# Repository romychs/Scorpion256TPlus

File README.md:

# Scorpion ZS-256 Turbo+

## Российский клон компьютера ZX Spectrum с улучшениями.

Компьютер разрабатывался и выпускался, под руководством Сергея Зонова, санкт-петербургской фирмой Scorpion с 1996 по 1998г.
Данная версия схемы, отревершена по файлам molodcov_alex, а затем и по плате Павла Рябцова известной как "Black Edition".
Изначально это была схема, которая упоминается как схема Черного кота. В создании схемы, большую помощь оказали труды savelij из темы про скорпиона 1024.

## Особенности:
- Z80B CPU, режим Turbo 7MHz, данный вариант хорошо работает с КМОП процессорами Z84C0020PEC.
- 256k DRAM, хорошо работают только импортные микросхемы типа 41256.
- Теневой Сервис-Монитор
- Музыкальный сопроцессор AY-3-8912.
- 2 Слота расширения ZX Bus.
- Контроллер дисковода Floppy-дисков с ФАПЧ.
- Старые микросхемы 565РТ5 заменены более доступными GAL16V8, GAL22V10.
- PROF ROM.
- Интерфейс Centronics для принтера.
- Интерфейс RS-232, но никто не проверял, работает ли?

[Принципиальная схема](Export/Schematic_Scorpion-256-Turbo_v16.2.8.pdf)

[Монтажная схема](Export/PCB_SILK_TOP_v16.2.8.pdf)

Печатная плата и герберы, получены, как побочный продукт при реверсе схемы и отличаются и от платы molodcov_alex и от платы Павла. Многие уже собирали платы версий до v16.2.3. 
Некоторые трассы укорочены, уменьшено число изгибов проводников, уменьшено число проводников между ножками процессора с 3-х до 2-х.
На плате нет краевых разъемов.

[Тема на форуме, по данному варианту компьютера](https://zx-pk.ru/threads/9195-scorpion-zs-256-turbo-restored)

[Чат ZS Scorpion  в Telegram](https://t.me/zs_scorpion)

## Внимание!
- На платах v16.2.4 и v16.2.5 на шелкографии обнаружена ошибка. Все транзисторы КТ315 и КТ361, нужно запаивать эмиттером в отверстие с квадратным падом.

## Изменения
- В версии v16.2, исправлено подключение GAL ФАПЧ контроллера дисковода. Несоответствие было обнаружено при сборке платы пользователем форума tigr101274. Исправлена печатная плата в соответствии со схемой, на печатной плате значительно расширены проводники питания за счет полигонов.
- В версии v16.2.1 исправлена ошибка, замеченная azx987sa, с сигналом строба интерфейса принтера.
- В версии v16.2.2 добавлен резистор R76, как в Scorpion ZS 1024 Turbo+ от savelij, для лучшего качества звука с AY. Убраны лишние дорожки и переходные отверстия, замеченные пользователем ponchik.
- В версии v16.2.3 изменена схема формирования сигнала DSR, по варианту, предложенному Jeckas Nameless. Изменены футпринты для транзисторов КТ315/КТ361 и некоторых конденсаторов. Перенесен диод VD2 для более удобного монтажа.
- В версии v16.2.4 подвинуты некоторые элементы для удобства сборки, заменен футпринт AY (ponchik). На разъем XP3 выведен сигнал SYNC и добавлен разъем X16 - выход частоты 14МГц. Добавлены конденсаторы по питанию, в районе чипов памяти (ponchik). Перенумерованы диоды, для соответствия оригиналу, H4 заменен на H5 в формирователе SYNC (RomanRom2). Добавлены перемычки для возможности выбора выхода звука AY ABC или BCA (участники [чата в Telegram](https://t.me/zs_scorpion)). 
- В версии v16.2.5 добавлены SMD-резисторы на задней стороны платы  для защиты порта музыкального сопроцессора (Jeckas Nameless). AY немного сдвинут дальше от слотов.
- В версии v16.2.6 Исправлена шелкография под транзисторами. Добавлены наименования для ~~диодов~~ стабилитронов. Подписаны GAL-ки.
- В версии v16.2.7 На нижнем краю платы, возле слотов шины, добавлен (опциональный) разъем питания, как на дисководах 3,5". 
На верхнем краю платы, там где были отверстия для конденсатора, теперь, отверстия либо для подпайки проводов, либо для установки разъема с расстоянием между выводами 2,54мм для подвода питания +5В. 
Рядом с этими отверстиями, добавлен блокировочный конденсатор С28. Так же, добавлен блокировочный конденсатор C29 на +12В питания шины. 
+12В на шине - это опция, она нужна редко для редких устройств, без необходимости, подавать это напряжение не нужно. Для питания Скорпиона, по прежнему, нужны только +5В.
Системный разъем сдвинут ближе к краю платы для возможности использования разъемов типа DIN-41612 32x2pin. Исправлены попутанные цвета на видеовыходе.
- В версии v16.2.8 Учтены пожелания Mikka_A и коллег после сборки скорпа v16.2.7 на стриме. Добавлена кнопка Reset на краю платы. Добавлены перемычки для подачи питания +5В и +12В на контакты слота как в Nemo-Bus. Отверстия под эмиттеры транзисторов - квадратиком, базы помечены буквой Б на шелкографии. Добавлен разъем для подключения скандаблера RGB-VGA. Редкий AY-3-8912 заменен на более доступный AY-3-8910.
- В версии v16.2.8а Заменены DD64 К555ИЕ10 на КР1533ИЕ10 и DD19, DD44 К555ИР16 на КР1533ИР16, DD61 К555ЛН5 на К155ЛН5.

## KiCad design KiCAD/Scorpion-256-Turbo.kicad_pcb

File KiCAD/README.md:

# Scorpion ZS-256 Turbo+

## Версия 16.2.8b от 1.11.2025

Версия, основанная на v16.2.8a мигрированная из EasyEDA в KiCADv9.0.

Есть некоторые изменения и дополнения, связанные с более жесткими правилами валидации схемы и платы в KiCAD. По идее, должно стать лучше :)

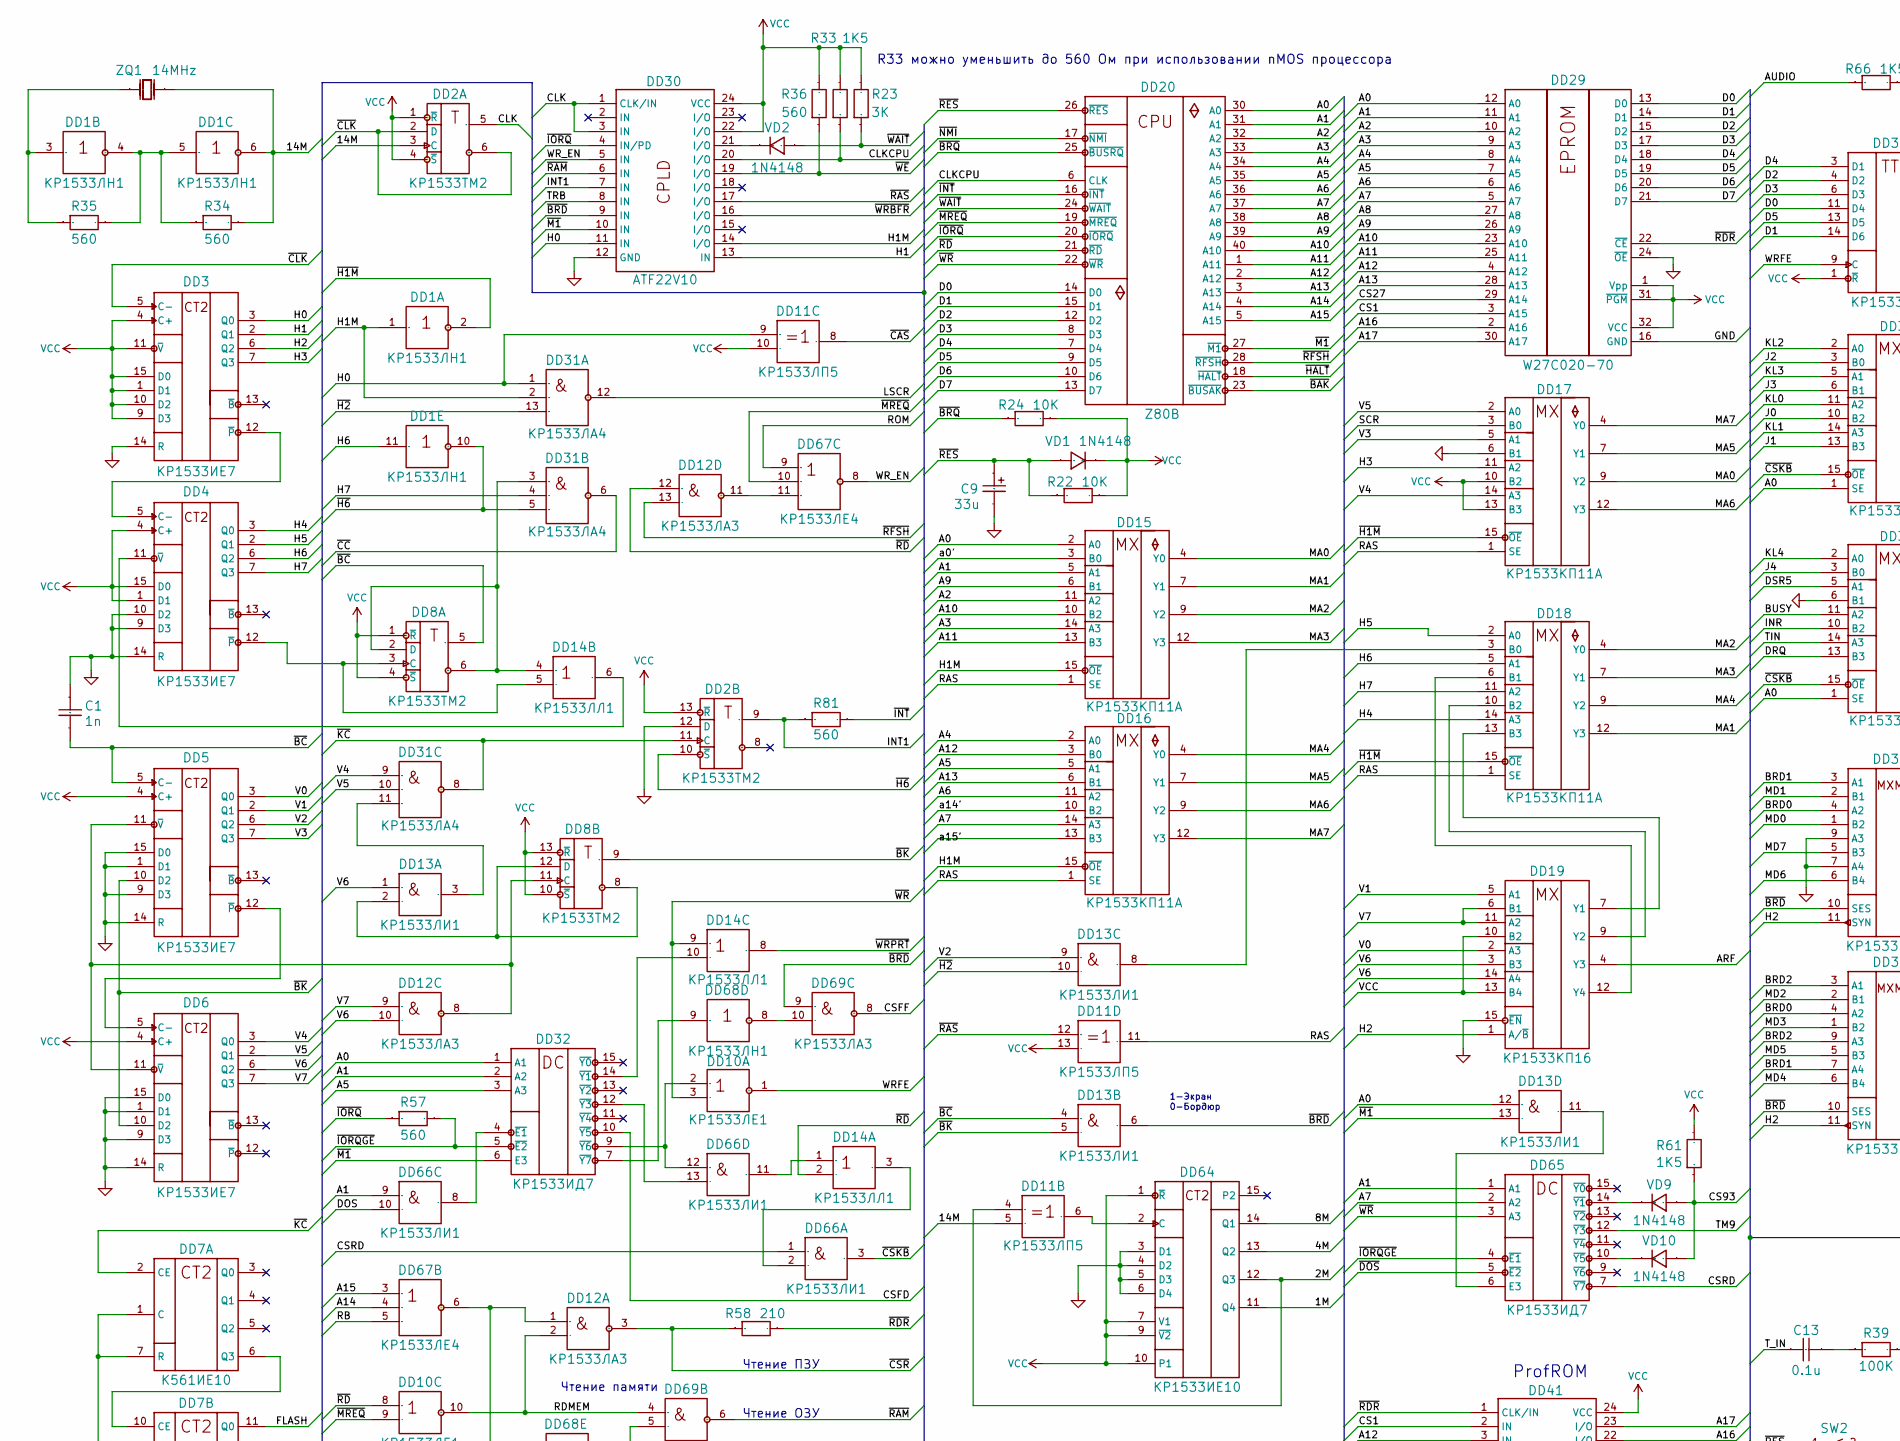
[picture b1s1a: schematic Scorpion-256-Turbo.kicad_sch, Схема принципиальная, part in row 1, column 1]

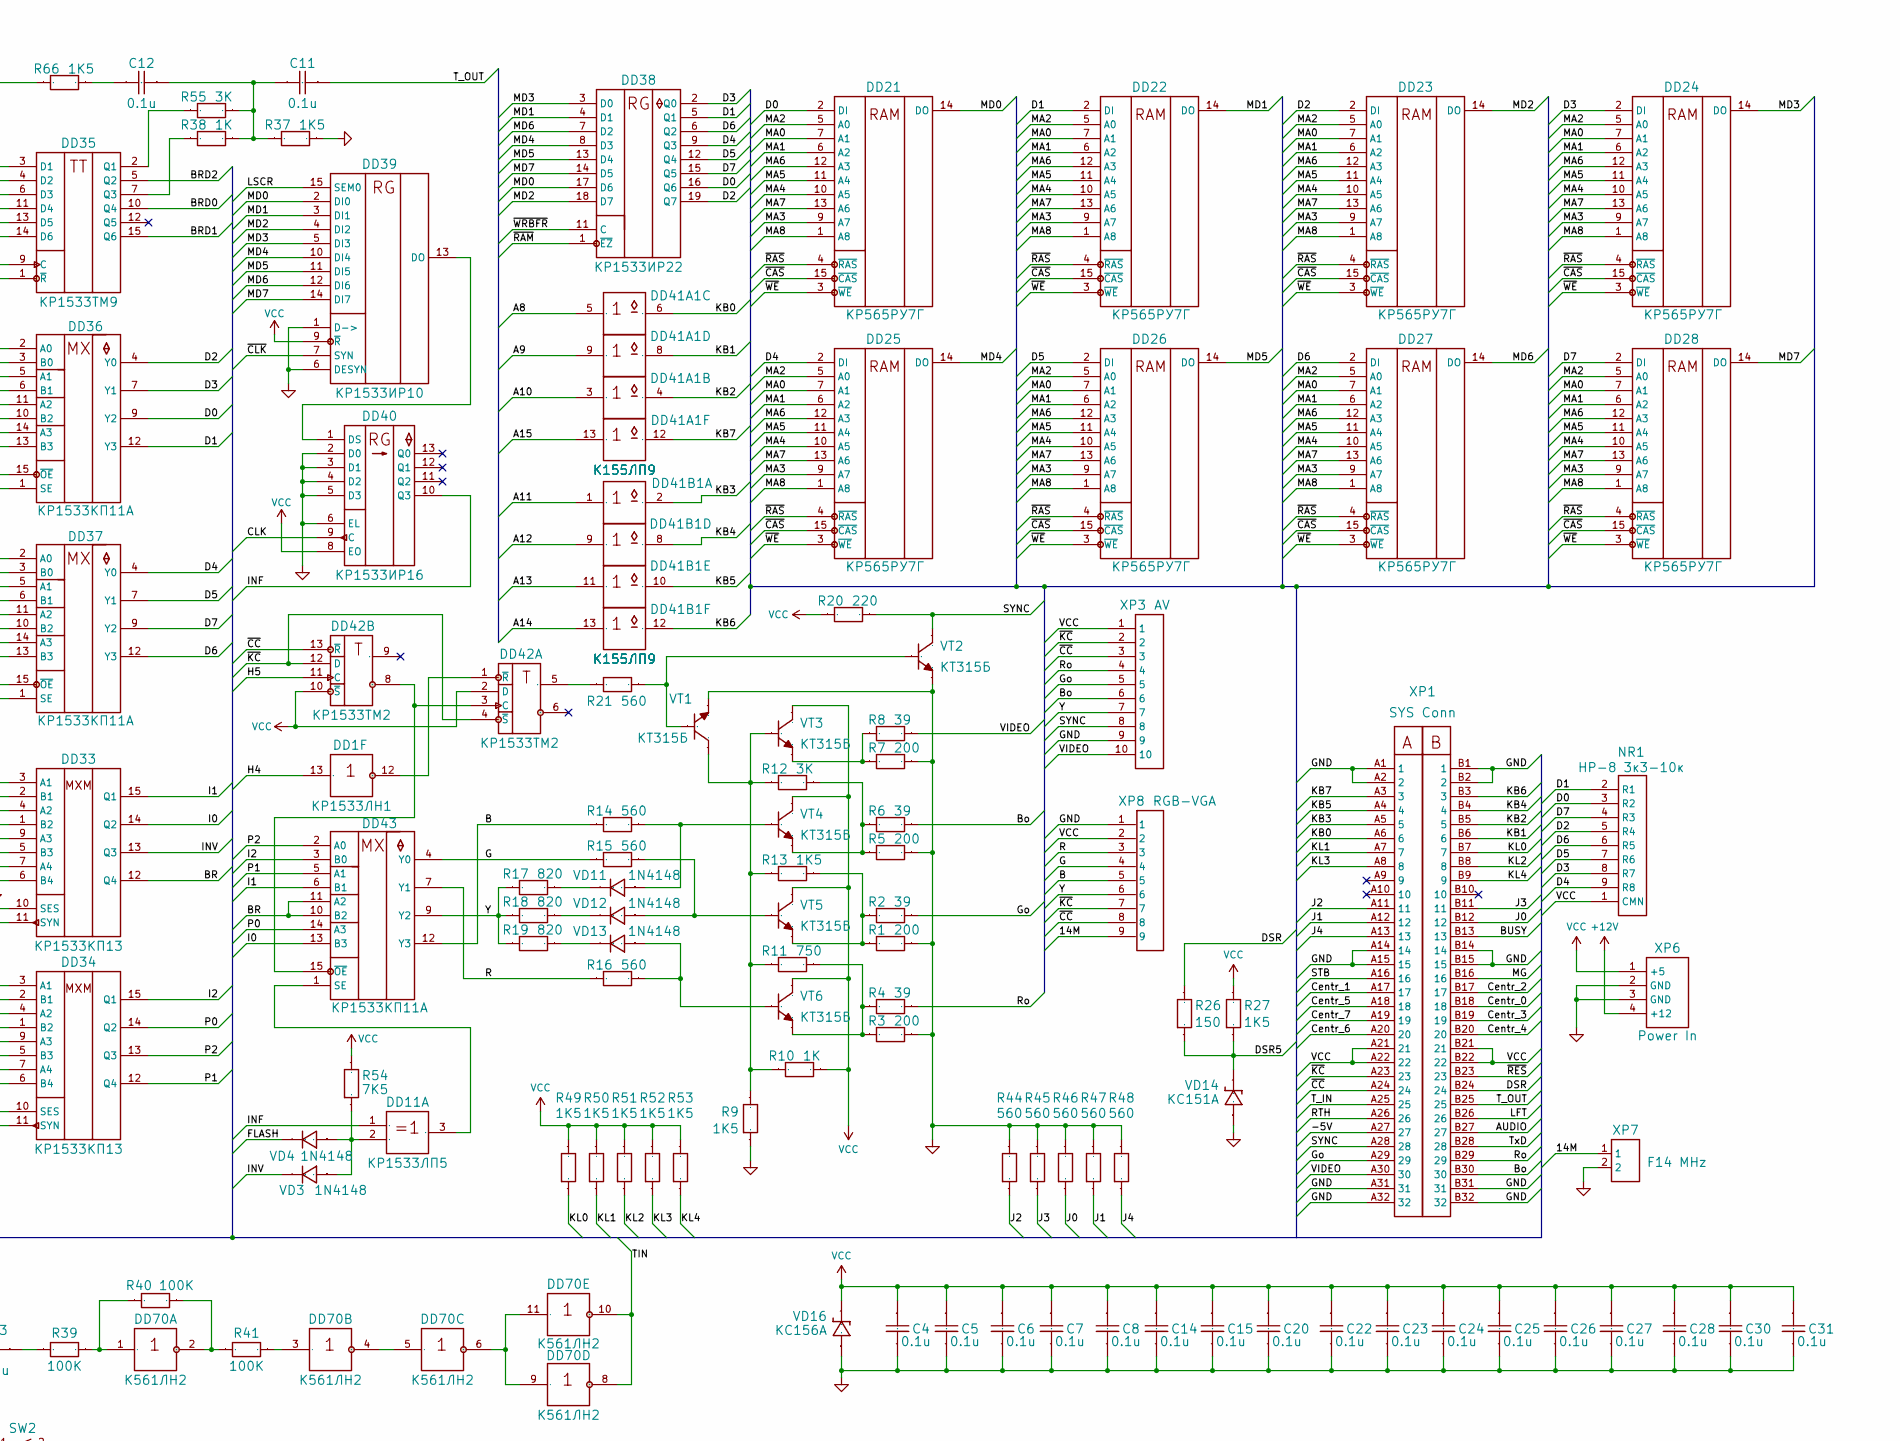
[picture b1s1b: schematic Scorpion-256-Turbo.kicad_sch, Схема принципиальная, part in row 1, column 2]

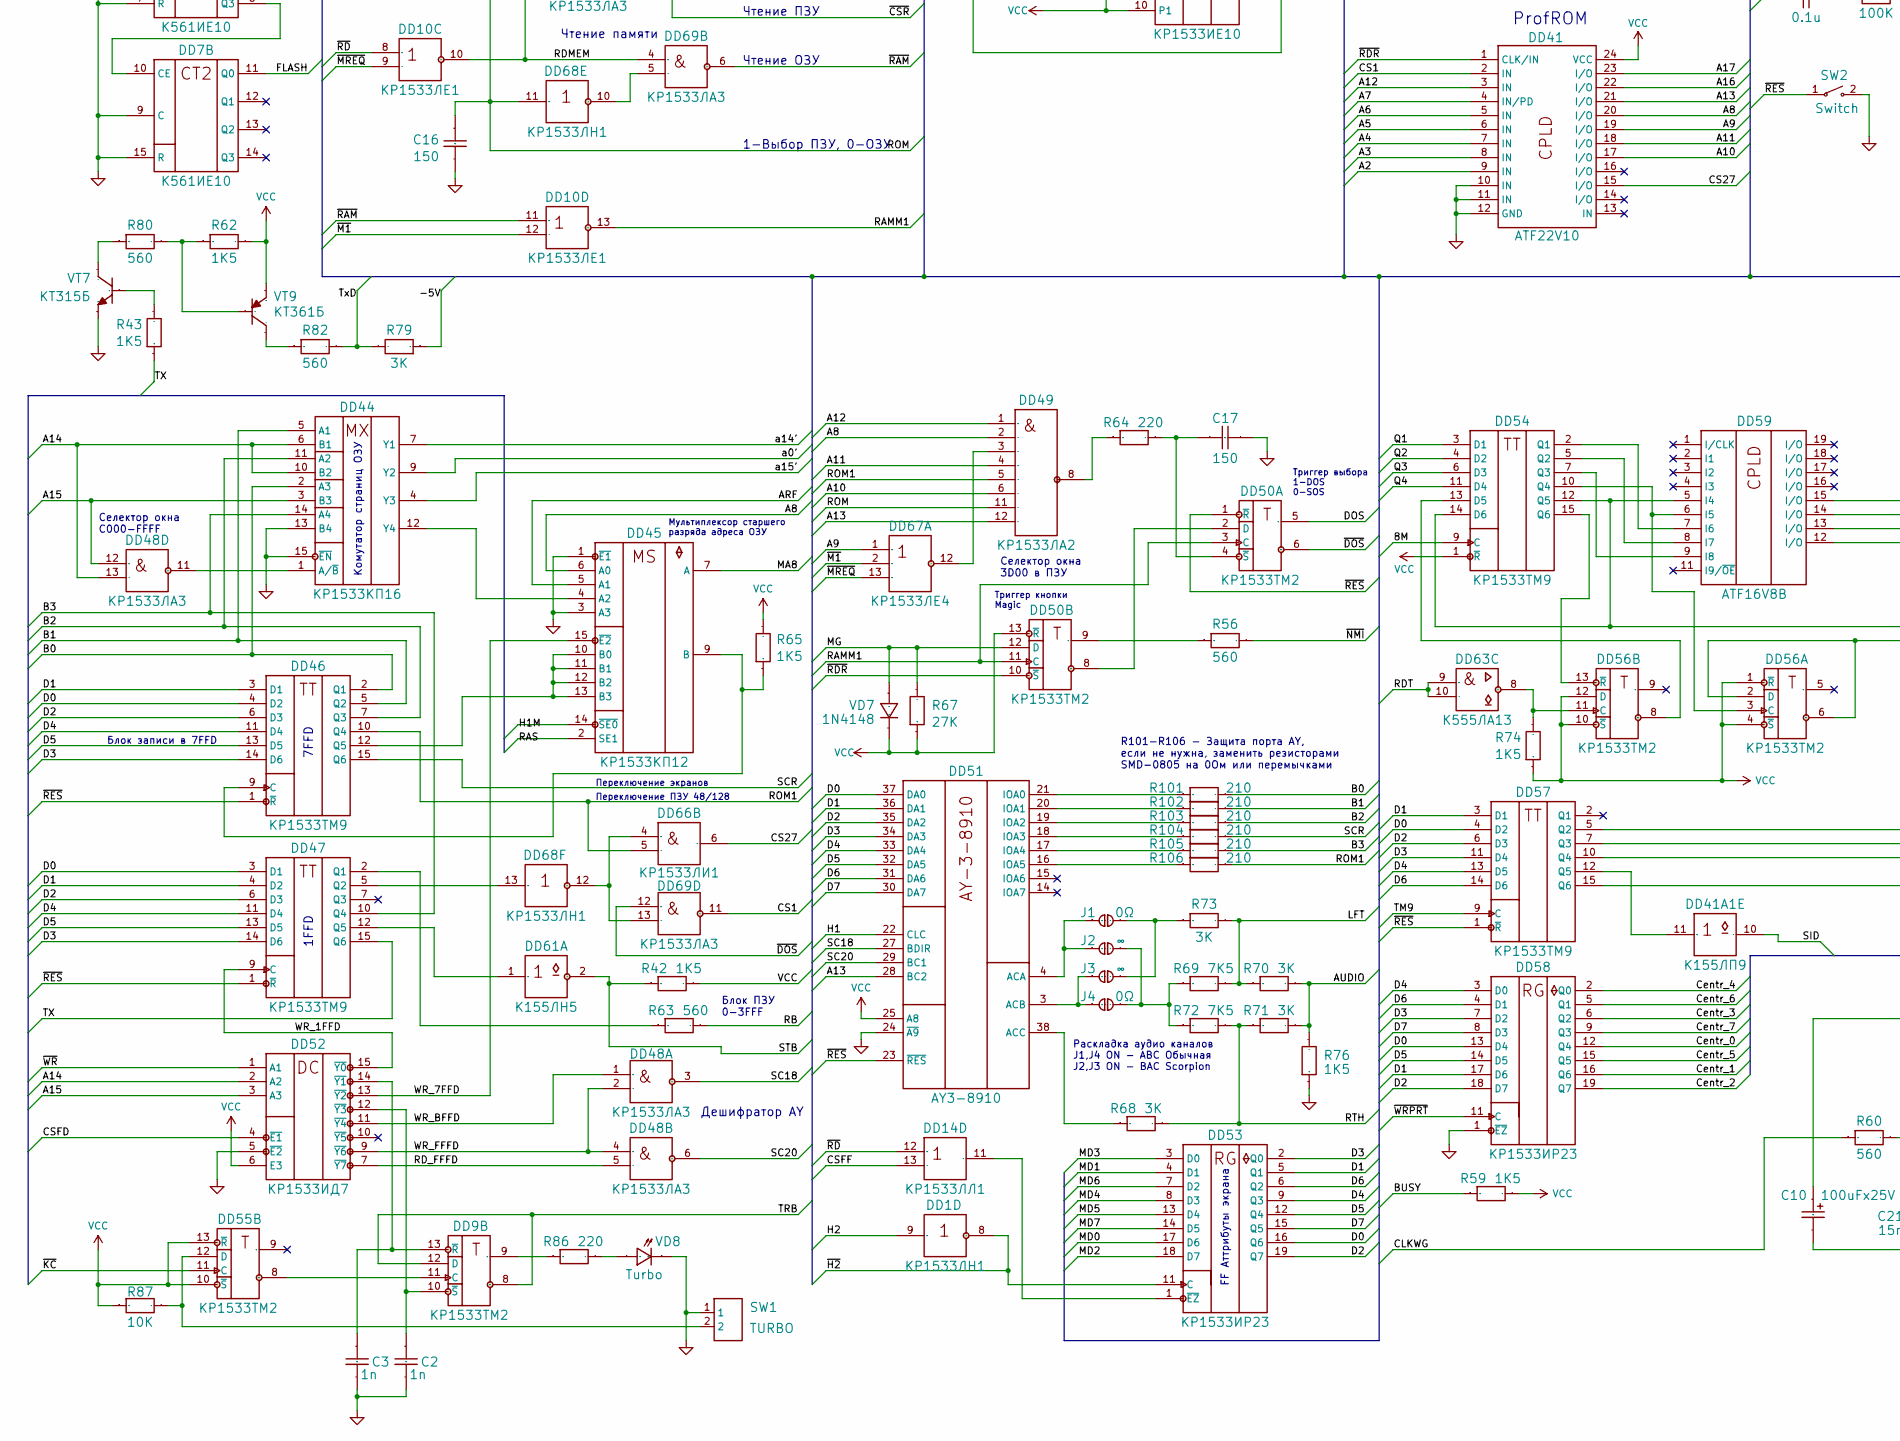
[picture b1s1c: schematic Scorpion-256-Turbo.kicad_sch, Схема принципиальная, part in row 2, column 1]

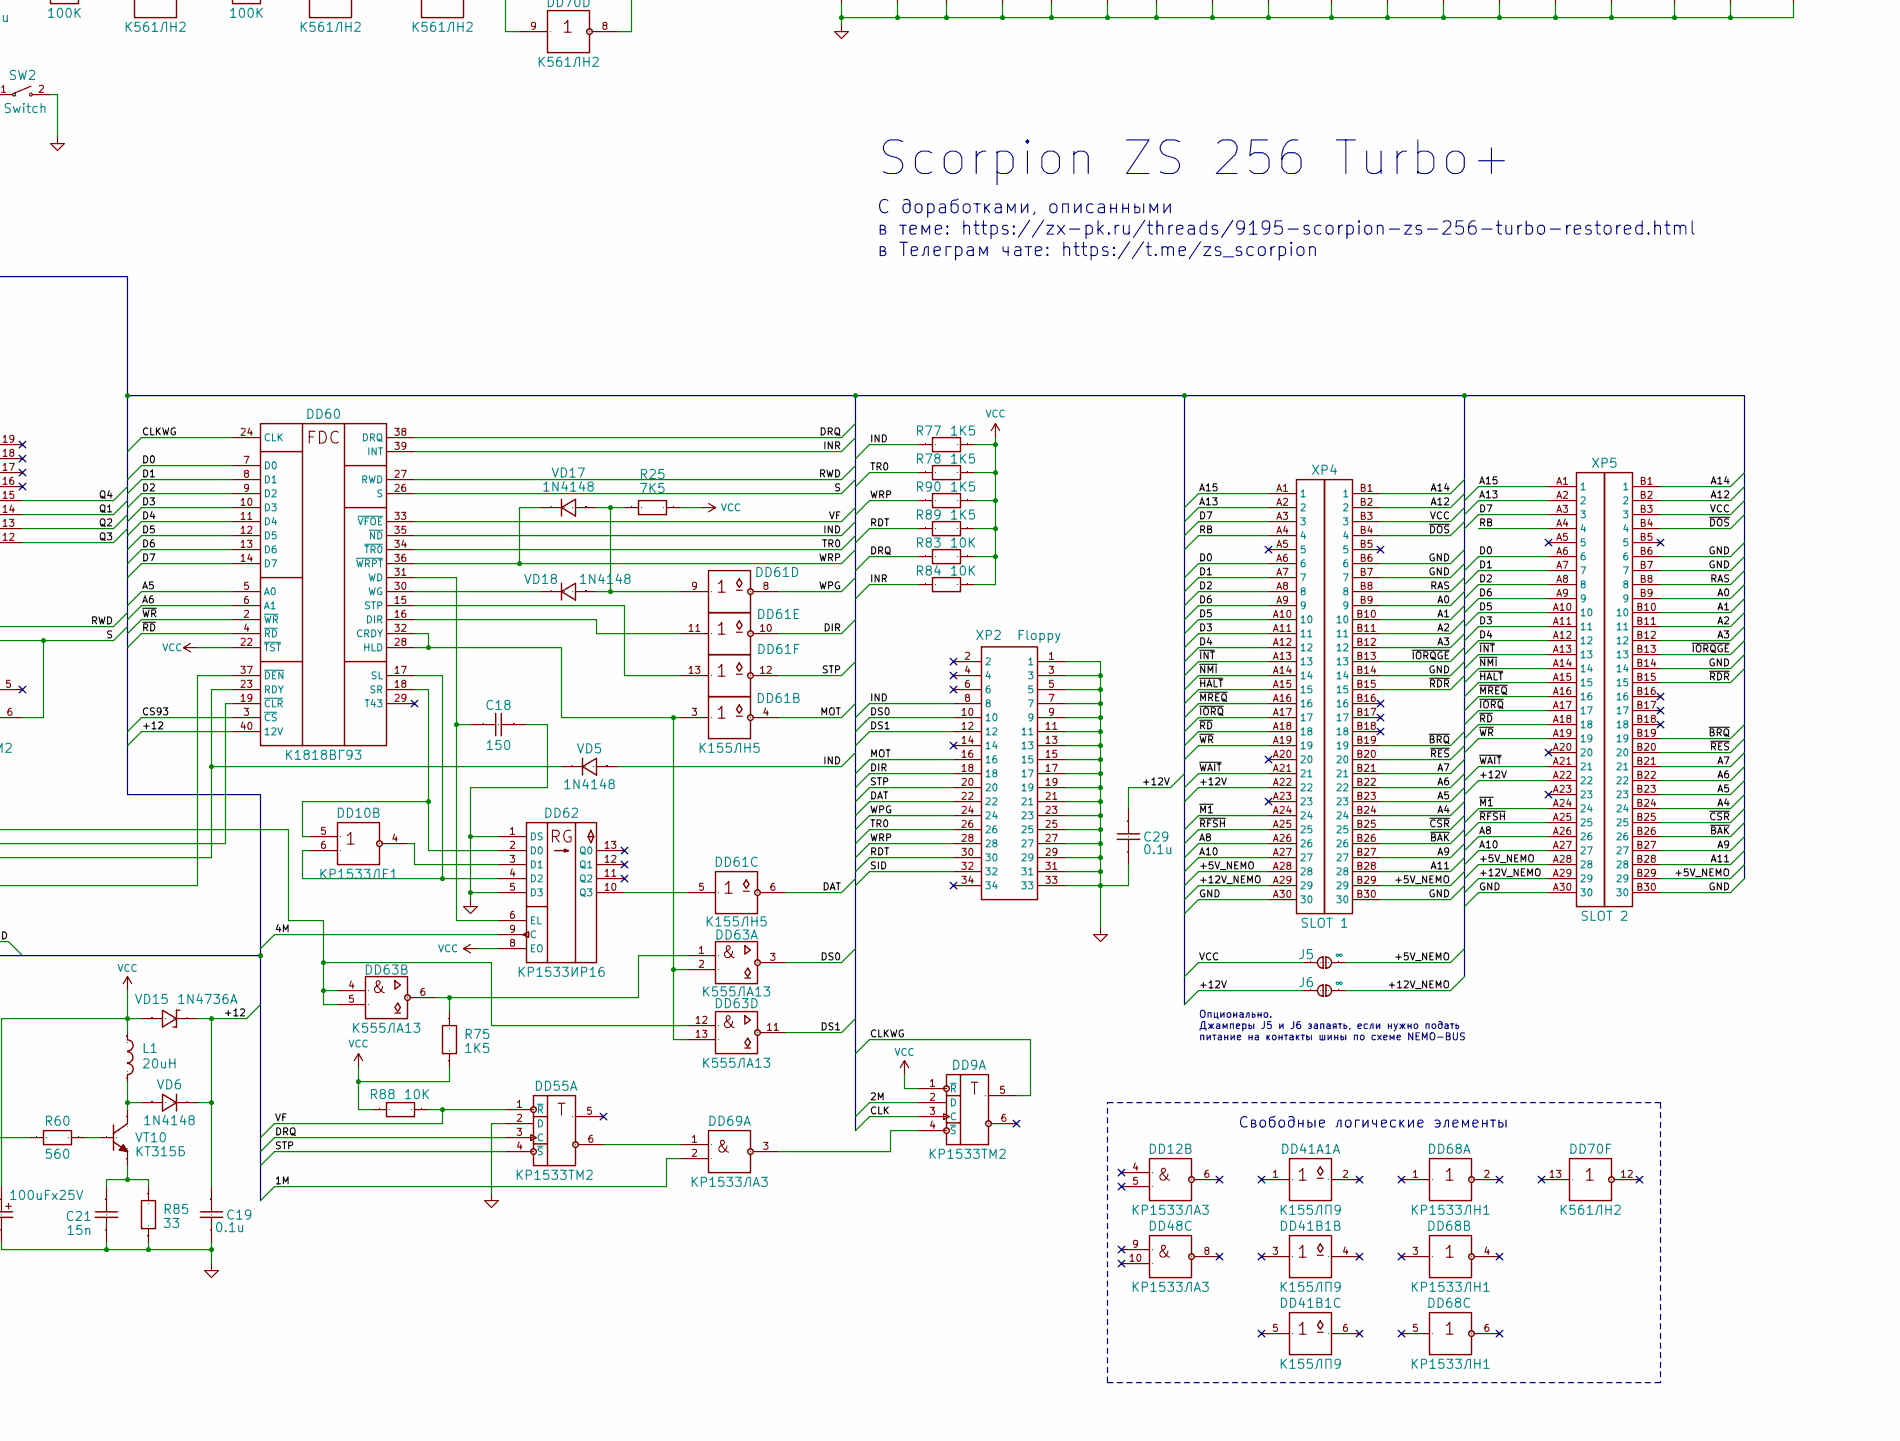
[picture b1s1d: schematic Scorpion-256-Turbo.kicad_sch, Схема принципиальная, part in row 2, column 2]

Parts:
C1, C2, C3: 1n; CAP-TH_L5.08
C4, C5, C6, C7, C8, C11, C12, C13, C14, C15, C19, C20, C22, C23, C24, C25, C26, C27, C28, C29, C30, C31: 0.1u; CAP-TH_L5.08
C9: 33u; CAP_P-TH-5x11-P2.54
C10: 100uFx25V; CAP_P-TH-5x11-P2.54
C16, C17, C18: 150; CAP-TH_L5.08
C21: 15n; CAP-TH_L5.08
DD1, DD68: КР1533ЛН1; DIP-14_W7.62mm
DD2, DD8, DD9, DD42, DD50, DD55, DD56: КР1533ТМ2; DIP-14_W7.62mm
DD3, DD4, DD5, DD6: КР1533ИЕ7; DIP-16_W7.62mm
DD7: К561ИЕ10; DIP-16_W7.62mm
DD10: КР1533ЛЕ1; DIP-14_W7.62mm
DD11: КР1533ЛП5; DIP-14_W7.62mm
DD12, DD48, DD69: КР1533ЛА3; DIP-14_W7.62mm
DD13, DD66: КР1533ЛИ1; DIP-14_W7.62mm
DD14: КР1533ЛЛ1; DIP-14_W7.62mm
DD15, DD16, DD17, DD18, DD36, DD37, DD43: КР1533КП11A; DIP-16_W7.62mm
DD19, DD44: КР1533КП16; DIP-16_W7.62mm
DD20: Z80B; DIP-40_W15.24mm_Socket
DD21, DD22, DD23, DD24, DD25, DD26, DD27, DD28: КР565РУ7Г; DIP-16_W7.62mm
DD29: W27C020-70; DIP-32_W15.24mm_Socket
DD30, DD41: ATF22V10; DIP-24_W7.62mm
DD31: КР1533ЛА4; DIP-14_W7.62mm
DD32, DD52, DD65: КР1533ИД7; DIP-16_W7.62mm
DD33, DD34: КР1533КП13; DIP-16_W7.62mm
DD35, DD46, DD47, DD54, DD57: КР1533ТМ9; DIP-16_W7.62mm
DD38: КР1533ИР22; DIP-20_STD_P7.2
DD39: КР1533ИР10; DIP-16_W7.62mm
DD40, DD62: КР1533ИР16; DIP-14_W7.62mm
DD41A1, DD41B1: К155ЛП9; DIP-14_W7.62mm
DD45: КР1533КП12; DIP-16_W7.62mm
DD49: КР1533ЛА2; DIP-14_W7.62mm
DD51: AY3-8910; DIP-40_W15.24mm_Socket
DD53, DD58: КР1533ИР23; DIP-20_STD_P7.2
DD59: ATF16V8B; DIP-20_W7.62mm
DD60: К1818ВГ93; DIP-40_W15.24mm_Socket
DD61: К155ЛН5; DIP-14_W7.62mm
DD63: К555ЛА13; DIP-14_W7.62mm
DD64: КР1533ИЕ10; DIP-16_W7.62mm
DD67: КР1533ЛЕ4; DIP-14_W7.62mm
DD70: К561ЛН2; DIP-14_W7.62mm
J1, J4: 0Ω; JUMP_0603
J2, J3, J5, J6: ∞; JUMP_0603
L1: 20uH; L-TH_L5.08
NR1: НР-8 3к3-10к; R_Array_SIP9
R1, R3, R5, R7: 200; RES_0.125W_P7.62
R2, R4, R6, R8: 39; RES_0.125W_P7.62
R9, R13, R27, R33, R37, R42, R43, R49, R50, R51, R52, R53, R59, R61, R62, R65, R66, R74, R75, R76, R77, R78, R89, R90: 1K5; RES_0.125W_P7.62
R10, R38: 1K; RES_0.125W_P7.62
R11: 750; RES_0.125W_P7.62
R12, R23, R55, R68, R70, R71, R73, R79: 3K; RES_0.125W_P7.62
R14, R15, R16, R21, R34, R35, R36, R44, R45, R46, R47, R48, R56, R57, R60, R63, R80, R81, R82: 560; RES_0.125W_P7.62
R17, R18, R19: 820; RES_0.125W_P7.62
R20, R64, R86: 220; RES_0.125W_P7.62
R22, R24, R83, R84, R87, R88: 10K; RES_0.125W_P7.62
R25, R54, R69, R72: 7K5; RES_0.125W_P7.62
R26: 150; RES_0.125W_P7.62
R39, R40, R41: 100K; RES_0.125W_P7.62
R58: 210; RES_0.125W_P7.62
R67: 27K; RES_0.125W_P7.62
R85: 33; RES_0.125W_P7.62
R101, R102, R103, R104, R105, R106: 210; R_0805_2012Metric_Pad1.20x1.40mm_HandSolder
SW1: TURBO; HDR-2P-M-P2.54
SW2: Switch; SW_Tactile_SPST_Angled_PTS645Vx39-2LFS
VD1, VD2, VD3, VD4, VD5, VD7, VD10, VD11, VD12, VD13, VD17, VD18: 1N4148; DIODE_TH_7.62; JLC_3DModel 982e0246bc4b4bfd9b52595e27e599f0
VD6: 1N4148; DIODE-TH_P10.16
VD8: Turbo; D-TH_LED_P2.54
VD9: 1N4148; DIODE-TH_P11.43
VD14: КС151А; DIODE_TH_7.62; JLC_3DModel 982e0246bc4b4bfd9b52595e27e599f0
VD15: 1N4736A; DIODE_TH_7.62; JLC_3DModel 982e0246bc4b4bfd9b52595e27e599f0
VD16: КС156А; DIODE_TH_7.62; JLC_3DModel 982e0246bc4b4bfd9b52595e27e599f0
VT1, VT2, VT3, VT4, VT5, VT6, VT7, VT10: КТ315Б; KT315_SLIM_STD; JLC_3DModel 4e458c2857b847c983e65719763eb26c
VT9: КТ361Б; KT315_SLIM_STD; JLC_3DModel 4e458c2857b847c983e65719763eb26c
XP1: SYS Conn; CONN_TH_DIN41612_32x2_ANG_INV
XP2: Floppy; IDC-Header_2x17_P2.54mm_Vertical
XP3: AV; PinSocket_1x10_P2.54mm_Vertical
XP4: SLOT 1; SL62_P2.54_R2
XP5: SLOT 2; SL62_P2.54_R2
XP6: Power In; JVC_MINI-TH-4P
XP7: F14 MHz; HDR-2P-M-P2.54
XP8: RGB-VGA; PinSocket_1x09_P2.54mm_Vertical
ZQ1: 14MHz; HC49-S

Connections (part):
+12V: C29.1, J6.1, XP4.A22 (22), XP5.A22 (22), XP6.4 (+12)
/1M: DD64.11 (Q4), DD69.2
/2M: DD9.2 (D), DD11.4 (1), DD64.12 (Q3)
/4M: DD62.9 (C), DD64.13 (Q2)
/8M: DD54.9 (C), DD64.14 (Q1)
/14M: DD1.6 (2), DD2.3 (С), DD11.5 (2), R34.2, XP7.1, XP8.9, ZQ1.1 (OSC1)
/+5V_NEMO: J5.2, XP4.A28 (28), XP4.B29 (29), XP5.A28 (28), XP5.B29 (29)
/+12: C19.1, DD60.40 (12V), VD6.2 (K), VD15.2 (K)
/+12V_NEMO: J6.2, XP4.A29 (29), XP5.A29 (29)
/-5V: R79.1, XP1.A27 (27)
/A0: DD13.12 (1), DD15.2 (A0), DD20.30 (A0), DD29.12 (A0), DD32.1 (A1), DD36.1 (SE), DD37.1 (SE), XP4.B9 (9), XP5.B9 (9)
/A1: DD15.5 (A1), DD20.31 (A1), DD29.11 (A1), DD32.2 (A2), DD65.1 (A1), DD66.9 (1), XP4.B10 (10), XP5.B10 (10)
/A2: DD15.11 (A2), DD20.32 (A2), DD29.10 (A2), DD41.9 (IN), XP4.B11 (11), XP5.B11 (11)
/A3: DD15.14 (A3), DD20.33 (A3), DD29.9 (A3), DD41.8 (IN), XP4.B12 (12), XP5.B12 (12)
/A4: DD16.2 (A0), DD20.34 (A4), DD29.8 (A4), DD41.7 (IN), XP4.B24 (24), XP5.B24 (24)
/A5: DD16.5 (A1), DD20.35 (A5), DD29.7 (A5), DD32.3 (A3), DD41.6 (IN), DD60.5 (A0), XP4.B23 (23), XP5.B23 (23)
/A6: DD16.11 (A2), DD20.36 (A6), DD29.6 (A6), DD41.5 (IN), DD60.6 (A1), XP4.B22 (22), XP5.B22 (22)
/A7: DD16.14 (A3), DD20.37 (A7), DD29.5 (A7), DD41.4 (IN/PD), DD65.2 (A2), XP4.B21 (21), XP5.B21 (21)
/A8: DD20.38 (A8), DD29.27 (A8), DD41.20 (I/O), DD41A1.5 (1), DD45.6 (A0), DD49.2, XP4.A26 (26), XP5.A26 (26)
/A9: DD15.6 (B1), DD20.39 (A9), DD29.26 (A9), DD41.19 (I/O), DD41A1.9 (1), DD67.1 (I1), XP4.B27 (27), XP5.B27 (27)
/A10: DD15.10 (B2), DD20.40 (A10), DD29.23 (A10), DD41.17 (I/O), DD41A1.3 (1), DD49.6, XP4.A27 (27), XP5.A27 (27)
/A11: DD15.13 (B3), DD20.1 (A11), DD29.25 (A11), DD41.18 (I/O), DD41B1.1, DD49.4, XP4.B28 (28), XP5.B28 (28)
/A12: DD16.3 (B0), DD20.2 (A12), DD29.4 (A12), DD41.3 (IN), DD41B1.9 (1), DD49.1, XP4.B2 (2), XP5.B2 (2)
/A13: DD16.6 (B1), DD20.3 (A13), DD29.28 (A13), DD41.21 (I/O), DD41B1.11 (1), DD49.12 (8), DD51.28 (BC2), XP4.A2 (2), XP5.A2 (2)
/A14: DD20.4 (A14), DD41B1.13 (1), DD44.6 (B1), DD44.10 (B2), DD48.13 (2), DD52.2 (A2), DD67.4 (I2), XP4.B1 (1), XP5.B1 (1)
/A15: DD20.5 (A15), DD41A1.13 (1), DD44.3 (B3), DD48.12 (1), DD52.3 (A3), DD67.3 (I1), XP4.A1 (1), XP5.A1 (1)
/A16: DD29.2 (A16), DD41.22 (I/O)
/A17: DD29.30 (A17), DD41.23 (I/O)
/ARF: DD19.4 (Y3), DD45.5 (A1)
/AUDIO: R66.1, R70.2, R71.2, R76.2, XP1.B27 (27)
/B: DD43.12 (Y3), R14.1, XP8.5
/B0: DD44.2 (A3), DD46.2 (Q1), R101.2
/B1: DD44.5 (A1), DD46.5 (Q2), R102.2
/B2: DD44.11 (A2), DD46.7 (Q3), R103.2
/B3: DD44.14 (A4), DD47.10 (Q4), R105.2
/BR: DD33.12 (Q4), DD43.10 (B2), DD43.11 (A2)
/BRD0: DD33.4 (A2), DD34.4 (A2), DD35.10 (Q4)
/BRD1: DD33.3 (A1), DD34.7 (A4), DD35.15 (Q6)
/BRD2: DD34.3 (A1), DD34.9 (A3), DD35.5 (Q2)
/BUSY: DD37.11 (A2), R59.1, XP1.B13 (13)
/Bo: R6.2, XP1.B30 (30), XP3.6
/CLK: DD2.5 (Q), DD9.3 (С), DD30.1 (CLK/IN), DD30.3 (IN), DD40.9 (C)
/CLKCPU: DD20.6 (CLK), DD30.20 (I/O), R33.1
/CLKWG: DD9.5 (Q), DD60.24 (CLK), R60.1
/CS1: DD29.3 (A15), DD41.2 (IN), DD69.11 (3)
/CS27: DD29.29 (A14), DD41.15 (I/O), DD66.6 (3)
/CS93: DD60.3 (~CS), R61.1, VD9.1 (A), VD10.1 (A)
/CSFD: DD32.10 (~Y5), DD52.4 (~E1)
/CSFF: DD14.13 (2), DD69.8 (3)
/CSRD: DD65.7 (~Y7), DD66.1
/Centr_0: DD58.12 (Q4), XP1.B18 (18)
/Centr_1: DD58.16 (Q6), XP1.A17 (17)
/Centr_2: DD58.19 (Q7), XP1.B17 (17)
/Centr_3: DD58.6 (Q2), XP1.B19 (19)
/Centr_4: DD58.2 (Q0), XP1.B20 (20)
/Centr_5: DD58.15 (Q5), XP1.A18 (18)
/Centr_6: DD58.5 (Q1), XP1.A20 (20)
/Centr_7: DD58.9 (Q3), XP1.A19 (19)
/D0: DD20.14 (D0), DD21.2 (DI), DD29.13 (D0), DD35.11 (D4), DD36.9 (Y2), DD38.16 (Q6), DD46.4 (D2), DD47.3 (D1), DD51.37 (DA0), DD53.16 (Q6), DD57.4 (D2), DD58.13 (D4), DD60.7 (D0), NR1.3 (R2), XP4.A6 (6), XP5.A6 (6)
/D1: DD20.15 (D1), DD22.2 (DI), DD29.14 (D1), DD35.14 (D6), DD36.12 (Y3), DD38.5 (Q1), DD46.3 (D1), DD47.4 (D2), DD51.36 (DA1), DD53.5 (Q1), DD57.3 (D1), DD58.17 (D6), DD60.8 (D1), NR1.2 (R1), XP4.A7 (7), XP5.A7 (7)
/D2: DD20.12 (D2), DD23.2 (DI), DD29.15 (D2), DD35.4 (D2), DD36.4 (Y0), DD38.19 (Q7), DD46.6 (D3), DD47.6 (D3), DD51.35 (DA2), DD53.19 (Q7), DD57.6 (D3), DD58.18 (D7), DD60.9 (D2), NR1.5 (R4), XP4.A8 (8), XP5.A8 (8)
/D3: DD20.8 (D3), DD24.2 (DI), DD29.17 (D3), DD35.6 (D3), DD36.7 (Y1), DD38.2 (Q0), DD46.14 (D6), DD47.14 (D6), DD51.34 (DA3), DD53.2 (Q0), DD57.11 (D4), DD58.7 (D2), DD60.10 (D3), NR1.8 (R7), XP4.A11 (11), XP5.A11 (11)
/D4: DD20.7 (D4), DD25.2 (DI), DD29.18 (D4), DD35.3 (D1), DD37.4 (Y0), DD38.9 (Q3), DD46.11 (D4), DD47.11 (D4), DD51.33 (DA4), DD53.9 (Q3), DD57.13 (D5), DD58.3 (D0), DD60.11 (D4), NR1.9 (R8), XP4.A12 (12), XP5.A12 (12)
/D5: DD20.9 (D5), DD26.2 (DI), DD29.19 (D5), DD35.13 (D5), DD37.7 (Y1), DD38.12 (Q4), DD46.13 (D5), DD47.13 (D5), DD51.32 (DA5), DD53.12 (Q4), DD58.14 (D5), DD60.12 (D5), NR1.7 (R6), XP4.A10 (10), XP5.A10 (10)
/D6: DD20.10 (D6), DD27.2 (DI), DD29.20 (D6), DD37.12 (Y3), DD38.6 (Q2), DD51.31 (DA6), DD53.6 (Q2), DD57.14 (D6), DD58.4 (D1), DD60.13 (D6), NR1.6 (R5), XP4.A9 (9), XP5.A9 (9)
/D7: DD20.13 (D7), DD28.2 (DI), DD29.21 (D7), DD37.9 (Y2), DD38.15 (Q5), DD51.30 (DA7), DD53.15 (Q5), DD58.8 (D3), DD60.14 (D7), NR1.4 (R3), XP4.A3 (3), XP5.A3 (3)
/DAT: DD61.6 (2), XP2.22
/DIR: DD61.10 (2), XP2.18
/DOS: DD50.5 (Q), DD66.10 (2)
/DRQ: DD37.13 (B3), DD55.3 (С), DD60.38 (DRQ), R83.1
/DS0: DD63.3, XP2.10
/DS1: DD63.11 (3), XP2.12
/DSR: R26.2, XP1.B24 (24)
/DSR5: DD37.5 (A1), R26.1, R27.1, VD14.2 (K)
/FLASH: DD7.11 (Q0), VD4.2 (K)
/G: DD43.4 (Y0), R15.1, XP8.4
/Go: R2.2, XP1.A29 (29), XP3.5
/H0: DD3.3 (Q0), DD11.9 (1), DD30.11 (IN), DD31.1 (I1)
/H1: DD3.2 (Q1), DD30.13 (IN), DD51.22 (CLC)
/H1M: DD1.1, DD15.15 (~OE), DD16.15 (~OE), DD30.14 (I/O), DD31.2 (I2), DD45.14 (~SE0)
/H2: DD1.9 (1), DD3.6 (Q2), DD19.1 (A/~B), DD33.11 (SYN), DD34.11 (SYN)
/H3: DD3.7 (Q3), DD17.11 (A2)
/H4: DD1.13 (1), DD4.3 (Q0), DD18.14 (A3)
/H5: DD4.2 (Q1), DD18.2 (A0), DD42.11 (С)
/H6: DD1.11 (1), DD4.6 (Q2), DD18.5 (A1)
/H7: DD4.7 (Q3), DD18.11 (A2), DD31.4 (I2)
/I0: DD33.14 (Q2), DD43.13 (B3)
/I1: DD33.15 (Q1), DD43.6 (B1)
/I2: DD34.15 (Q1), DD43.3 (B0)
/IND: DD60.35 (~ND), R77.1, VD5.1 (A), XP2.8
/INF: DD11.1, DD40.10 (Q3)
/INR: DD37.10 (B2), DD60.39 (INT), R84.1
/INT1: DD2.9 (Q), DD30.7 (IN), R81.1
/INV: DD33.13 (Q3), VD3.2 (K)
/J0: DD36.10 (B2), R46.1, XP1.B12 (12)
/J1: DD36.13 (B3), R47.1, XP1.A12 (12)
/J2: DD36.3 (B0), R44.1, XP1.A11 (11)
/J3: DD36.6 (B1), R45.1, XP1.B11 (11)
/J4: DD37.3 (B0), R48.1, XP1.A13 (13)
/KB0: DD41A1.6 (2), XP1.A6 (6)
/KB1: DD41A1.8 (2), XP1.B6 (6)
/KB2: DD41A1.4 (2), XP1.B5 (5)
/KB3: DD41B1.2, XP1.A5 (5)
/KB4: DD41B1.8 (2), XP1.B4 (4)
/KB5: DD41B1.10 (2), XP1.A4 (4)
/KB6: DD41B1.12 (2), XP1.B3 (3)
/KB7: DD41A1.12 (2), XP1.A3 (3)
/KL0: DD36.11 (A2), R49.1, XP1.B7 (7)
/KL1: DD36.14 (A3), R50.1, XP1.A7 (7)
/KL2: DD36.2 (A0), R51.1, XP1.B8 (8)
/KL3: DD36.5 (A1), R52.1, XP1.A8 (8)
/KL4: DD37.2 (A0), R53.1, XP1.B9 (9)
/LFT: R69.2, R70.1, R73.2, XP1.B26 (26)
/LSCR: DD31.12 (O), DD39.15 (SEM0)
/MA0: DD15.4 (Y0), DD17.9 (Y2), DD21.7 (A1), DD22.7 (A1), DD23.7 (A1), DD24.7 (A1), DD25.7 (A1), DD26.7 (A1), DD27.7 (A1), DD28.7 (A1)
/MA1: DD15.7 (Y1), DD18.12 (Y3), DD21.6 (A2), DD22.6 (A2), DD23.6 (A2), DD24.6 (A2), DD25.6 (A2), DD26.6 (A2), DD27.6 (A2), DD28.6 (A2)
/MA2: DD15.9 (Y2), DD18.4 (Y0), DD21.5 (A0), DD22.5 (A0), DD23.5 (A0), DD24.5 (A0), DD25.5 (A0), DD26.5 (A0), DD27.5 (A0), DD28.5 (A0)
/MA3: DD15.12 (Y3), DD18.7 (Y1), DD21.9 (A7), DD22.9 (A7), DD23.9 (A7), DD24.9 (A7), DD25.9 (A7), DD26.9 (A7), DD27.9 (A7), DD28.9 (A7)
/MA4: DD16.4 (Y0), DD18.9 (Y2), DD21.10 (A5), DD22.10 (A5), DD23.10 (A5), DD24.10 (A5), DD25.10 (A5), DD26.10 (A5), DD27.10 (A5), DD28.10 (A5)
/MA5: DD16.7 (Y1), DD17.7 (Y1), DD21.11 (A4), DD22.11 (A4), DD23.11 (A4), DD24.11 (A4), DD25.11 (A4), DD26.11 (A4), DD27.11 (A4), DD28.11 (A4)
/MA6: DD16.9 (Y2), DD17.12 (Y3), DD21.12 (A3), DD22.12 (A3), DD23.12 (A3), DD24.12 (A3), DD25.12 (A3), DD26.12 (A3), DD27.12 (A3), DD28.12 (A3)
/MA7: DD16.12 (Y3), DD17.4 (Y0), DD21.13 (A6), DD22.13 (A6), DD23.13 (A6), DD24.13 (A6), DD25.13 (A6), DD26.13 (A6), DD27.13 (A6), DD28.13 (A6)
/MA8: DD21.1 (A8), DD22.1 (A8), DD23.1 (A8), DD24.1 (A8), DD25.1 (A8), DD26.1 (A8), DD27.1 (A8), DD28.1 (A8), DD45.7 (A)
/MD0: DD21.14 (DO), DD33.1 (B2), DD38.17 (D6), DD39.2 (DI0), DD53.17 (D6)
/MD1: DD22.14 (DO), DD33.2 (B1), DD38.4 (D1), DD39.3 (DI1), DD53.4 (D1)
/MD2: DD23.14 (DO), DD34.2 (B1), DD38.18 (D7), DD39.4 (DI2), DD53.18 (D7)
/MD3: DD24.14 (DO), DD34.1 (B2), DD38.3 (D0), DD39.5 (DI3), DD53.3 (D0)
/MD4: DD25.14 (DO), DD34.6 (B4), DD38.8 (D3), DD39.10 (DI4), DD53.8 (D3)
/MD5: DD26.14 (DO), DD34.5 (B3), DD38.13 (D4), DD39.11 (DI5), DD53.13 (D4)
/MD6: DD27.14 (DO), DD33.6 (B4), DD38.7 (D2), DD39.12 (DI6), DD53.7 (D2)
/MD7: DD28.14 (DO), DD33.5 (B3), DD38.14 (D5), DD39.14 (DI7), DD53.14 (D5)
/MG: DD50.12 (D), R67.2, VD7.1 (A), XP1.B16 (16)
/MOT: DD61.4 (2), XP2.16
/P0: DD34.14 (Q2), DD43.14 (A3)
/P1: DD34.12 (Q4), DD43.5 (A1)
/P2: DD34.13 (Q3), DD43.2 (A0)
/Q1: DD54.3 (D1), DD59.14 (I/O)
/Q2: DD54.4 (D2), DD59.13 (I/O)
/Q3: DD54.6 (D3), DD59.12 (I/O)
/Q4: DD54.11 (D4), DD59.15 (I/O)
/R: DD43.7 (Y1), R16.1, XP8.3
/RAMM1: DD10.13 (3), DD50.3 (С), DD50.11 (С)
/RAS: DD11.11 (3), DD15.1 (SE), DD16.1 (SE), DD17.1 (SE), DD18.1 (SE), DD45.2 (SE1), XP4.B8 (8), XP5.B8 (8)
/RB: DD67.5 (I3), R63.2, XP4.A4 (4), XP5.A4 (4)
/RDMEM: DD10.10 (3), DD12.2, DD69.4 (1)
/RDT: DD63.9 (1), DD63.10 (2), R89.1, XP2.30
/RD_FFFD: DD48.5 (2), DD52.7 (~Y7)
/ROM: C16.1, DD12.1, DD49.11 (7), DD67.6 (O), DD67.9 (I1), DD68.11 (1)
/ROM1: DD46.10 (Q4), DD49.5, DD66.5 (2), R106.2
/RTH: R68.2, R71.1, R72.2, XP1.A26 (26)
/RWD: DD54.12 (Q5), DD54.14 (D6), DD59.5 (I4), DD60.27 (RWD)
/Ro: R4.2, XP1.B29 (29), XP3.4
/S: DD56.2 (D), DD56.6 (~Q), DD60.26 (S)
/SC18: DD48.3, DD51.27 (BDIR)
/SC20: DD48.6 (3), DD51.29 (BC1)
/SCR: DD17.3 (B0), DD46.15 (Q6), R104.2
/SID: DD41A1.10 (2), XP2.32
/STB: DD61.2, R42.1, XP1.A16 (16)
/STP: DD55.4 (~S), DD61.12 (2), XP2.20
/SYNC: R20.2, VT2.2 (C), XP1.A28 (28), XP3.8
/TIN: DD37.14 (A3), DD70.8 (O), DD70.10 (O)
/TM9: DD57.9 (C), DD65.12 (~Y3)
/TR0: DD60.34 (~TR0), R78.1, XP2.26
/TRB: DD9.8 (~Q), DD9.12 (D), DD30.8 (IN)
/TX: DD47.15 (Q6), R43.1
/T_IN: C13.2, XP1.A25 (25)
/T_OUT: C11.1, XP1.B25 (25)
/TxD: R79.2, R82.2, XP1.B28 (28)
/V0: DD5.3 (Q0), DD19.2 (A3)
/V1: DD5.2 (Q1), DD19.5 (A1)
/V2: DD5.6 (Q2), DD13.9 (1)
/V3: DD5.7 (Q3), DD17.5 (A1)
/V4: DD6.3 (Q0), DD17.14 (A3), DD31.9 (I1)
/V5: DD6.2 (Q1), DD17.2 (A0), DD31.10 (I2)
/V6: DD6.6 (Q2), DD12.10 (2), DD13.1, DD19.3 (B3), DD19.14 (A4)
/V7: DD6.7 (Q3), DD12.9 (1), DD19.6 (B1), DD19.11 (A2)
/VF: DD55.1 (~R), DD60.33 (~VFOE), R88.2
/VIDEO: R8.2, XP1.A30 (30), XP3.10
/WPG: DD61.8 (2), XP2.24
/WRFE: DD10.1 (3), DD35.9 (C)
/WRP: DD60.36 (~WRPT), R90.1, VD17.2 (K), XP2.28
/WR_1FFD: DD47.9 (C), DD52.15 (~Y0)
/WR_7FFD: DD45.15 (~E2), DD52.13 (~Y2)
/WR_BFFD: DD48.1, DD52.11 (~Y4)
/WR_EN: DD30.5 (IN), DD67.8 (O)
/WR_FFFD: DD48.2, DD48.4 (1), DD52.9 (~Y6)
/Y: DD43.9 (Y2), R17.1, R18.1, R19.1, XP3.7, XP8.6
/a0': DD15.3 (B0), DD44.9 (Y2)
/a14': DD16.10 (B2), DD44.7 (Y1)
/a15': DD16.13 (B3), DD44.4 (Y3)
/~BAK: DD20.23 (~BUSAK), XP4.B26 (26), XP5.B26 (26)
/~BC: C1.2, DD5.5 (C-), DD8.5 (Q), DD13.4 (1)
/~BK: DD5.10 (D2), DD6.10 (D2), DD8.9 (Q), DD13.5 (2)
/~BRD: DD13.6 (3), DD30.9 (IN), DD33.10 (SES), DD34.10 (SES), DD69.9 (1)
/~BRQ: DD20.25 (~BUSRQ), R24.1, XP4.B19 (19), XP5.B19 (19)
/~CAS: DD11.8 (3), DD21.15 (~CAS), DD22.15 (~CAS), DD23.15 (~CAS), DD24.15 (~CAS), DD25.15 (~CAS), DD26.15 (~CAS), DD27.15 (~CAS), DD28.15 (~CAS)
/~CC: DD31.6 (O), DD42.13 (~R), XP1.A24 (24), XP3.3, XP8.8
/~CLK: DD2.2 (D), DD2.6 (~Q), DD3.5 (C-), DD39.7 (SYN)
/~CSKB: DD36.15 (~OE), DD37.15 (~OE), DD66.3
/~CSR: DD12.3, R58.1, XP4.B25 (25), XP5.B25 (25)
/~DOS: DD50.6 (~Q), DD65.5 (~E2), DD69.12 (1), XP4.B4 (4), XP5.B4 (4)
/~H1M: DD1.2, DD17.15 (~OE), DD18.15 (~OE)
/~H2: DD1.8 (2), DD13.10 (2), DD31.13 (I3), DD53.11 (C)
/~H6: DD1.10 (2), DD2.10 (~S), DD31.5 (I3)
/~HALT: DD20.18 (~HALT), XP4.A15 (15), XP5.A15 (15)
/~INT: DD20.16 (~INT), R81.2, XP4.A13 (13), XP5.A13 (13)
/~IORQGE: DD32.5 (~E2), DD65.4 (~E1), R57.2, XP4.B13 (13), XP5.B13 (13)
/~IORQ: DD20.20 (~IORQ), DD30.4 (IN/PD), R57.1, XP4.A17 (17), XP5.A17 (17)
/~KC: DD2.11 (С), DD7.2 (CE), DD31.8 (O), DD42.4 (~S), DD42.12 (D), DD55.11 (С), XP1.A23 (23), XP3.2, XP8.7
/~M1: DD10.12 (2), DD13.13 (2), DD20.27 (~M1), DD30.10 (IN), DD32.6 (E3), DD67.2 (I2), XP4.A24 (24), XP5.A24 (24)
/~MREQ: DD10.9 (2), DD20.19 (~MREQ), DD67.10 (I2), DD67.13 (I3), XP4.A16 (16), XP5.A16 (16)
/~NMI: DD20.17 (~NMI), R56.2, XP4.A14 (14), XP5.A14 (14)
/~RAM: DD10.11 (1), DD30.6 (IN), DD38.1 (~EZ), DD69.6 (3)
/~RAS: DD11.12 (1), DD21.4 (~RAS), DD22.4 (~RAS), DD23.4 (~RAS), DD24.4 (~RAS), DD25.4 (~RAS), DD26.4 (~RAS), DD27.4 (~RAS), DD28.4 (~RAS), DD30.17 (I/O)
/~RDR: DD29.22 (~CE), DD41.1 (CLK/IN), DD50.10 (~S), R58.2, XP4.B15 (15), XP5.B15 (15)
/~RD: DD10.8 (1), DD12.12 (1), DD14.2, DD14.12 (1), DD20.21 (~RD), DD60.4 (~RD), XP4.A18 (18), XP5.A18 (18)
/~RES: C9.1, DD20.26 (~RES), DD46.1 (~R), DD47.1 (~R), DD50.1 (~R), DD51.23 (~RES), DD57.1 (~R), R22.1, SW2.1, VD1.1 (A), XP1.B23 (23), XP4.B20 (20), XP5.B20 (20)
/~RFSH: DD12.13 (2), DD20.28 (~RFSH), XP4.A25 (25), XP5.A25 (25)
/~WAIT: DD20.24 (~WAIT), R23.1, VD2.1 (A), XP4.A21 (21), XP5.A21 (21)
/~WE: DD21.3 (~WE), DD22.3 (~WE), DD23.3 (~WE), DD24.3 (~WE), DD25.3 (~WE), DD26.3 (~WE), DD27.3 (~WE), DD28.3 (~WE), DD30.19 (I/O), R36.1
/~WRBFR: DD30.16 (I/O), DD38.11 (C)
/~WRPRT: DD14.8 (3), DD58.11 (C)
/~WR: DD10.3 (2), DD14.9 (1), DD20.22 (~WR), DD52.1 (A1), DD60.2 (~WR), DD65.3 (A3), XP4.A19 (19), XP5.A19 (19)
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
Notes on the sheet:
Чтение ПЗУ
Селектор окна C000-FFFF
1FFD
Свободные логические элементы
Триггер выбора 1-DOS 0-SOS
Селектор окна 3D00 в ПЗУ
R33 можно уменьшить до 560 Ом при использовании nMOS процессора
Комутатор страниц ОЗУ
7FFD
Блок записи в 7FFD
1-Экран 0-Бордюр
Чтение памяти
ProfROM
Раскладка аудио каналов J1,J4 ON - ABC Обычная J2,J3 ON - BAC Scorpion
Чтение ОЗУ
FF Аттрибуты экрана
1-Выбор ПЗУ, 0-ОЗУ
Блок ПЗУ 0-3FFF
Scorpion ZS 256 Turbo+
Переключение экранов
Переключение ПЗУ 48/128
Дешифратор AY
R101-R106 - Защита порта AY, если не нужна, заменить резисторами SMD-0805 на 0Ом или перемычками
Триггер кнопки Magic
Мультиплексор старшего разряда адреса ОЗУ
С доработками, описанными в теме: https://zx-pk.ru/threads/9195-scorpion-zs-256-turbo-restored.html в Телеграм чате: https://t.me/zs_scorpion
Опционально. Джамперы J5 и J6 запаять, если нужно подать питание на контакты шины по схеме NEMO-BUS
